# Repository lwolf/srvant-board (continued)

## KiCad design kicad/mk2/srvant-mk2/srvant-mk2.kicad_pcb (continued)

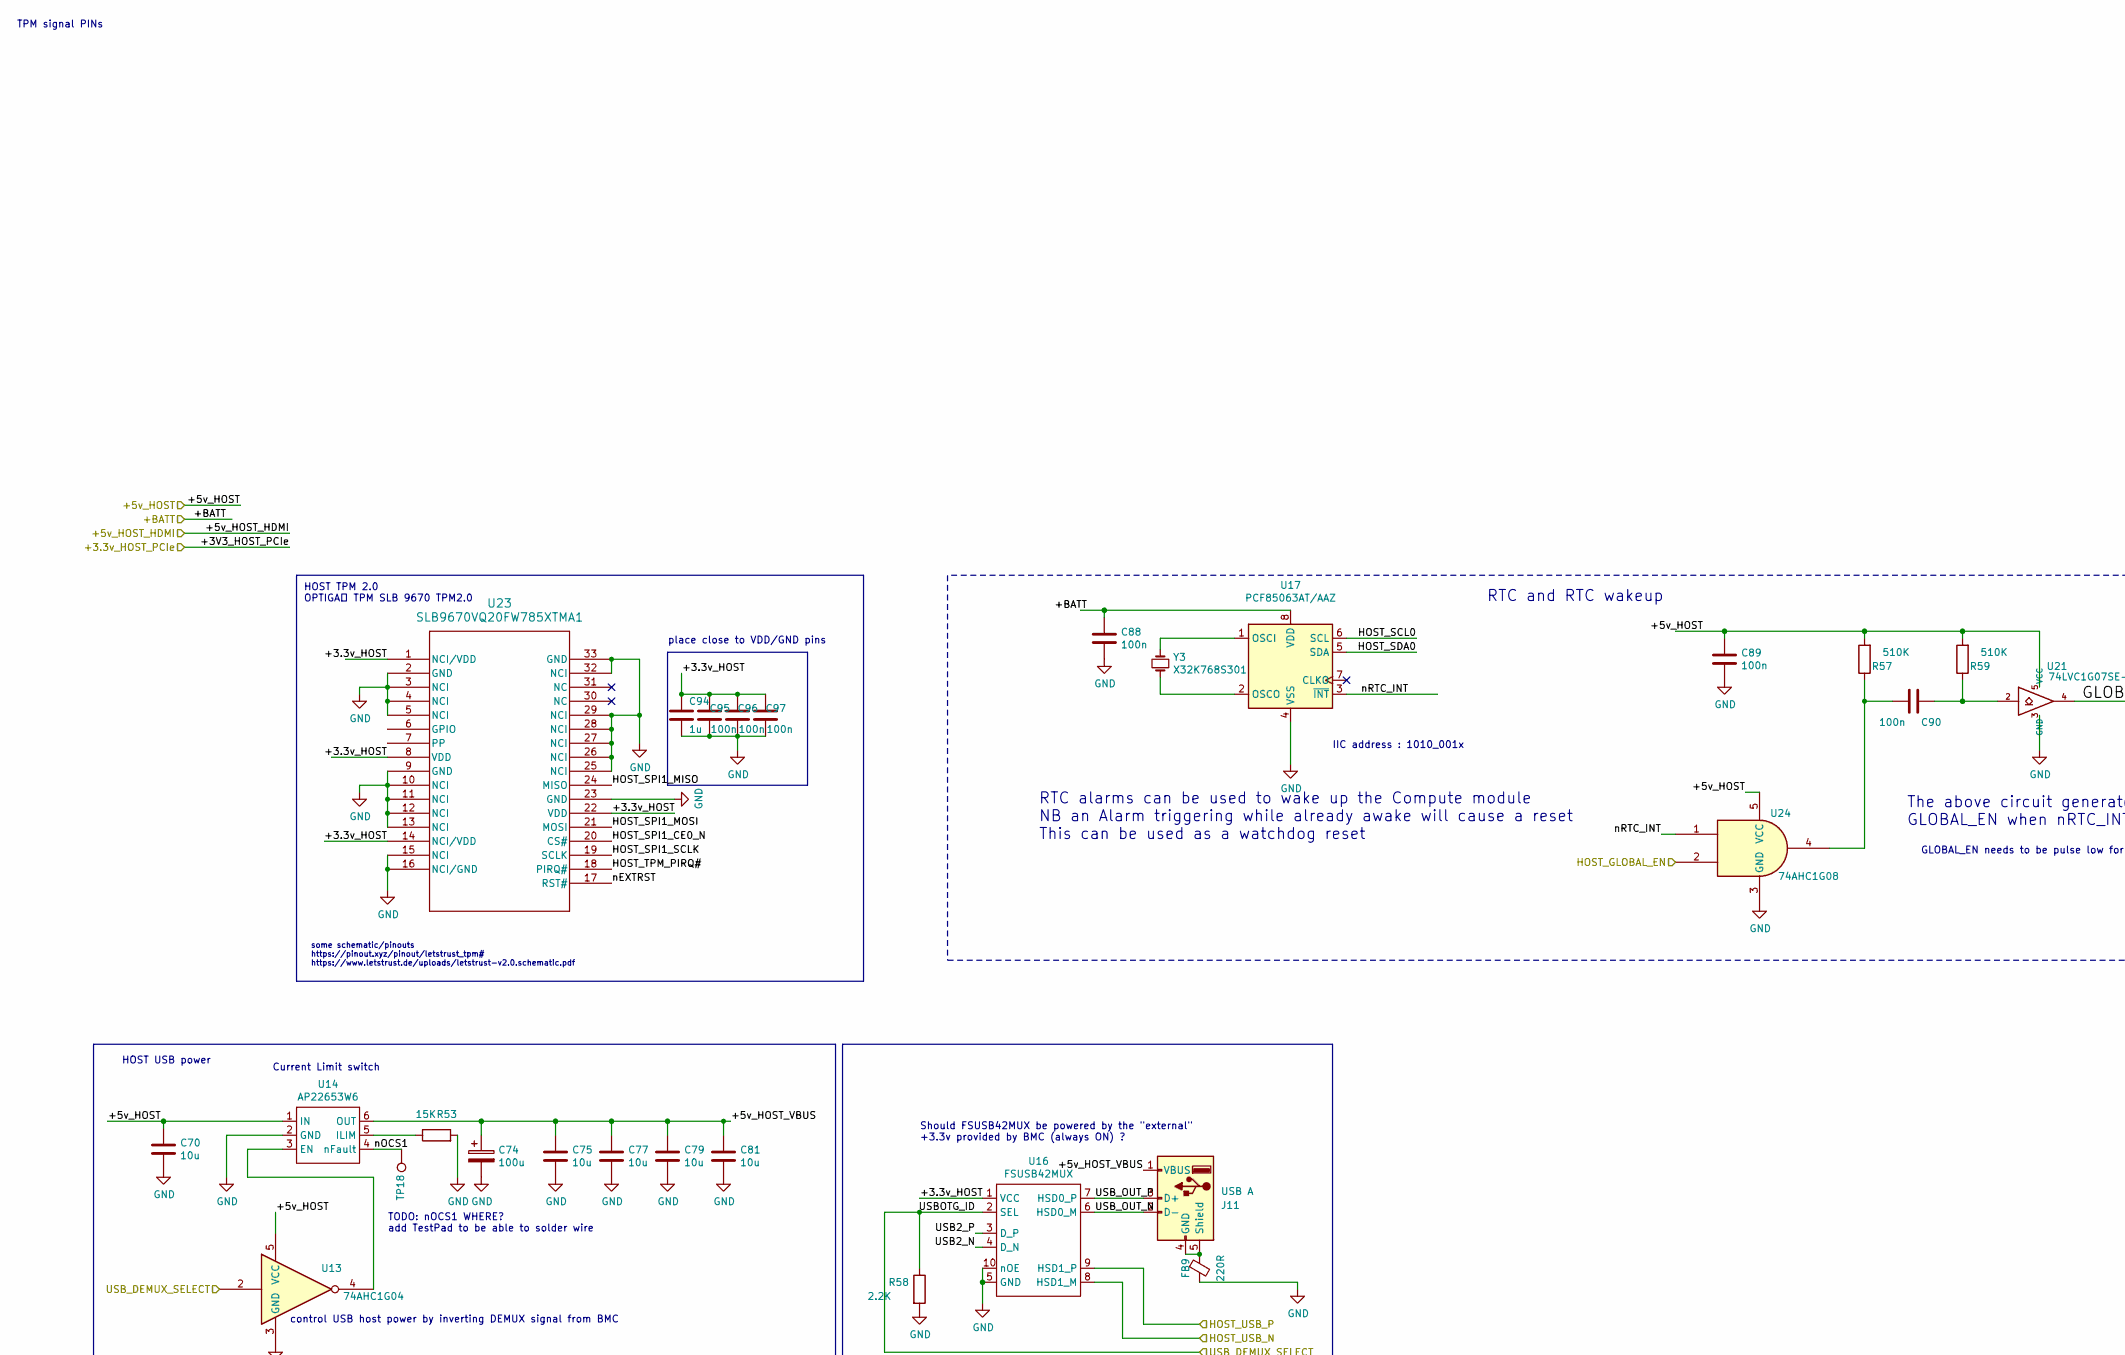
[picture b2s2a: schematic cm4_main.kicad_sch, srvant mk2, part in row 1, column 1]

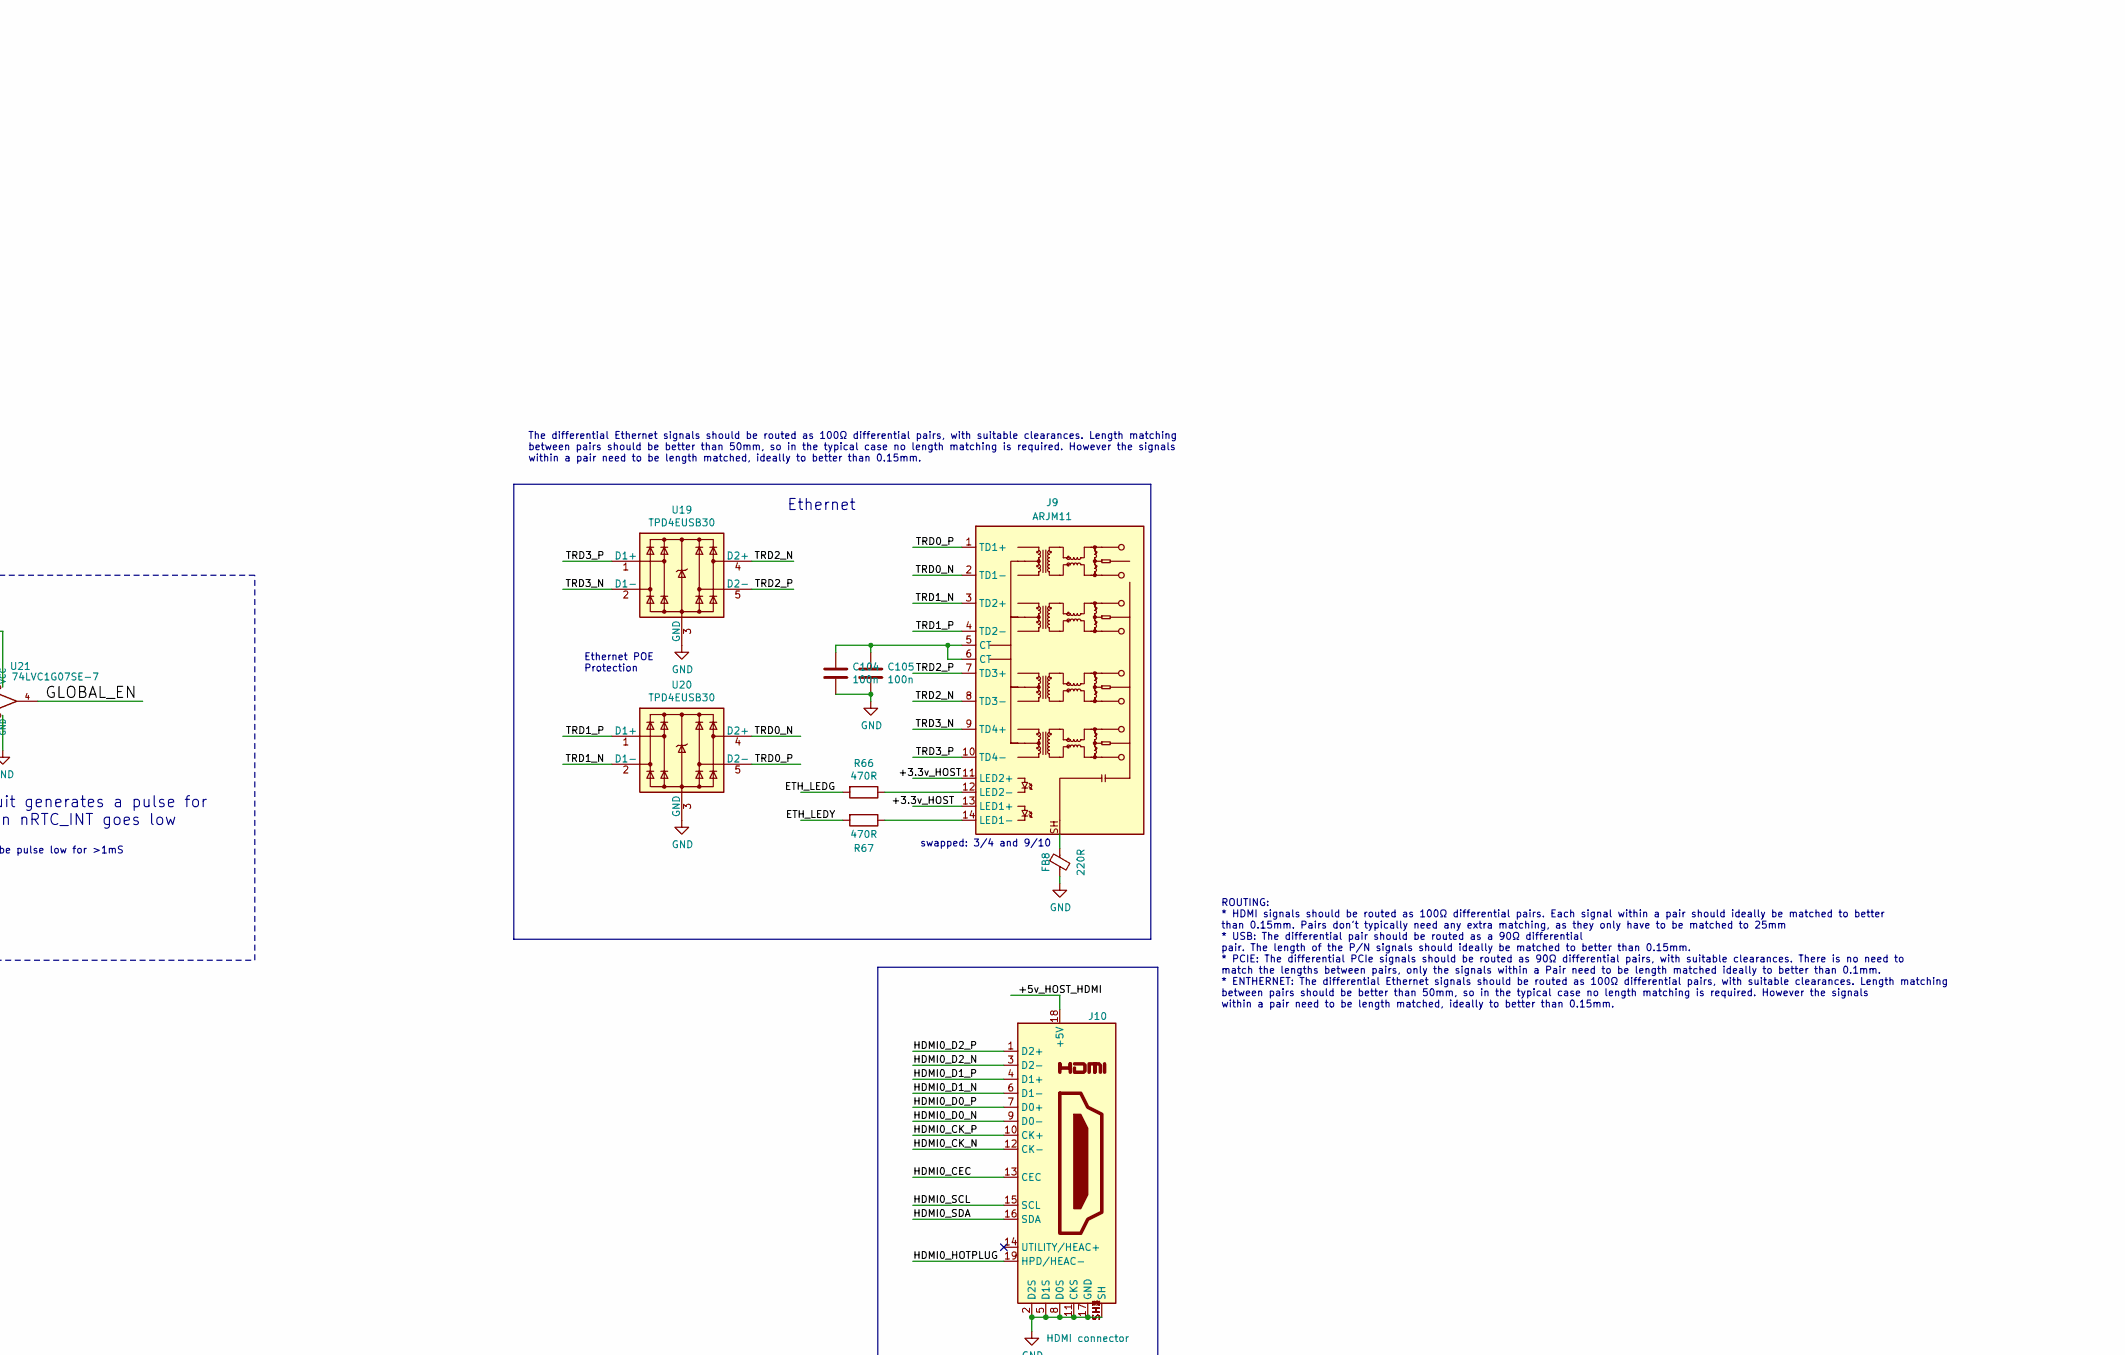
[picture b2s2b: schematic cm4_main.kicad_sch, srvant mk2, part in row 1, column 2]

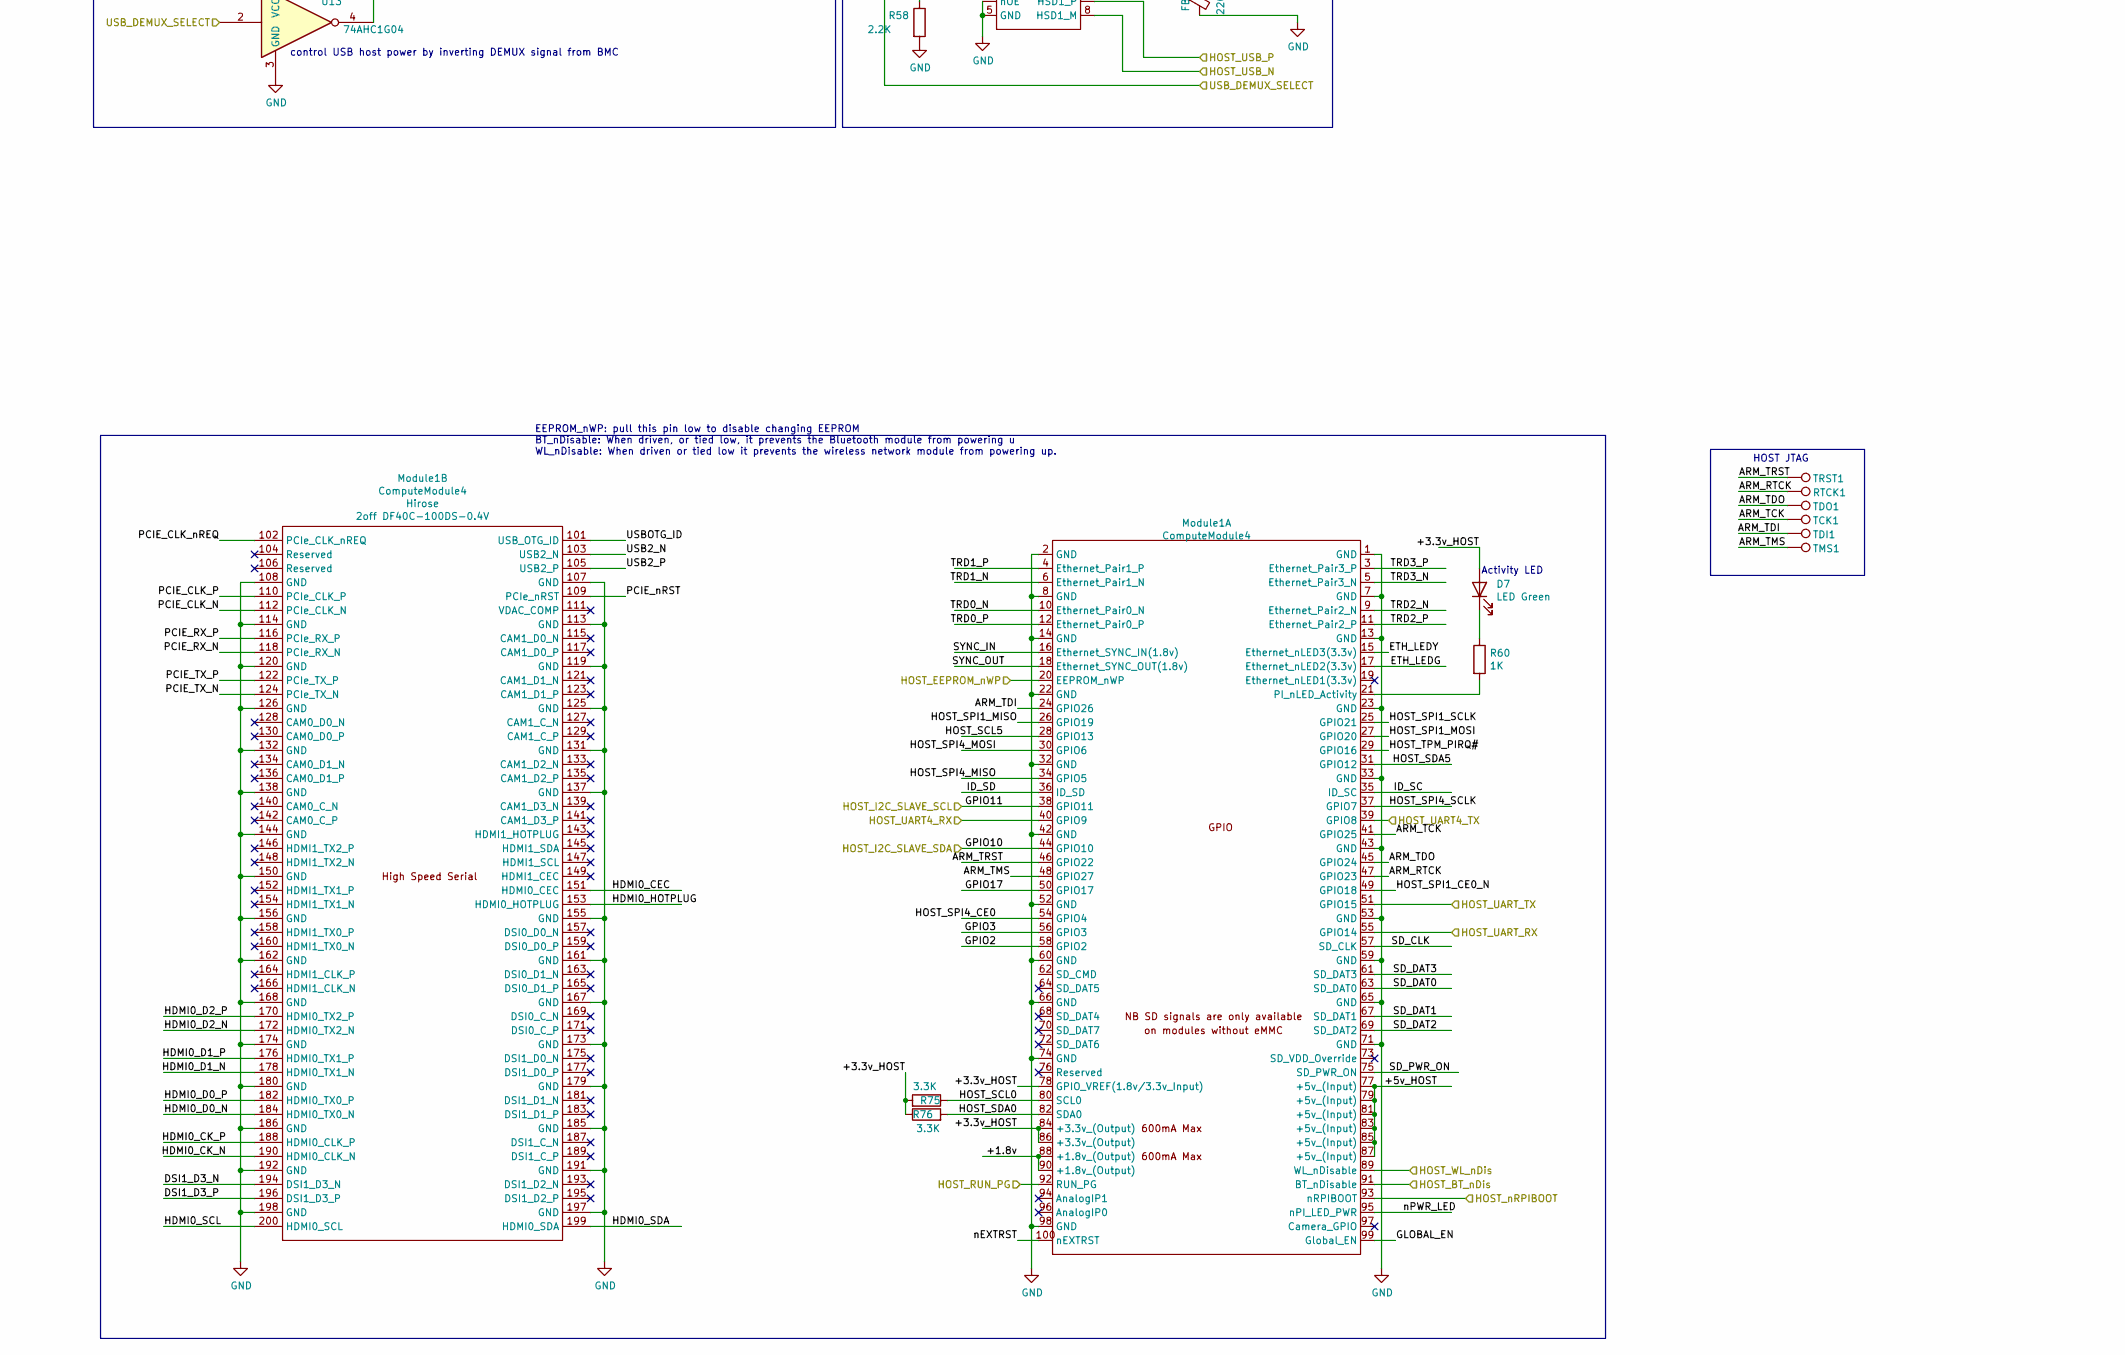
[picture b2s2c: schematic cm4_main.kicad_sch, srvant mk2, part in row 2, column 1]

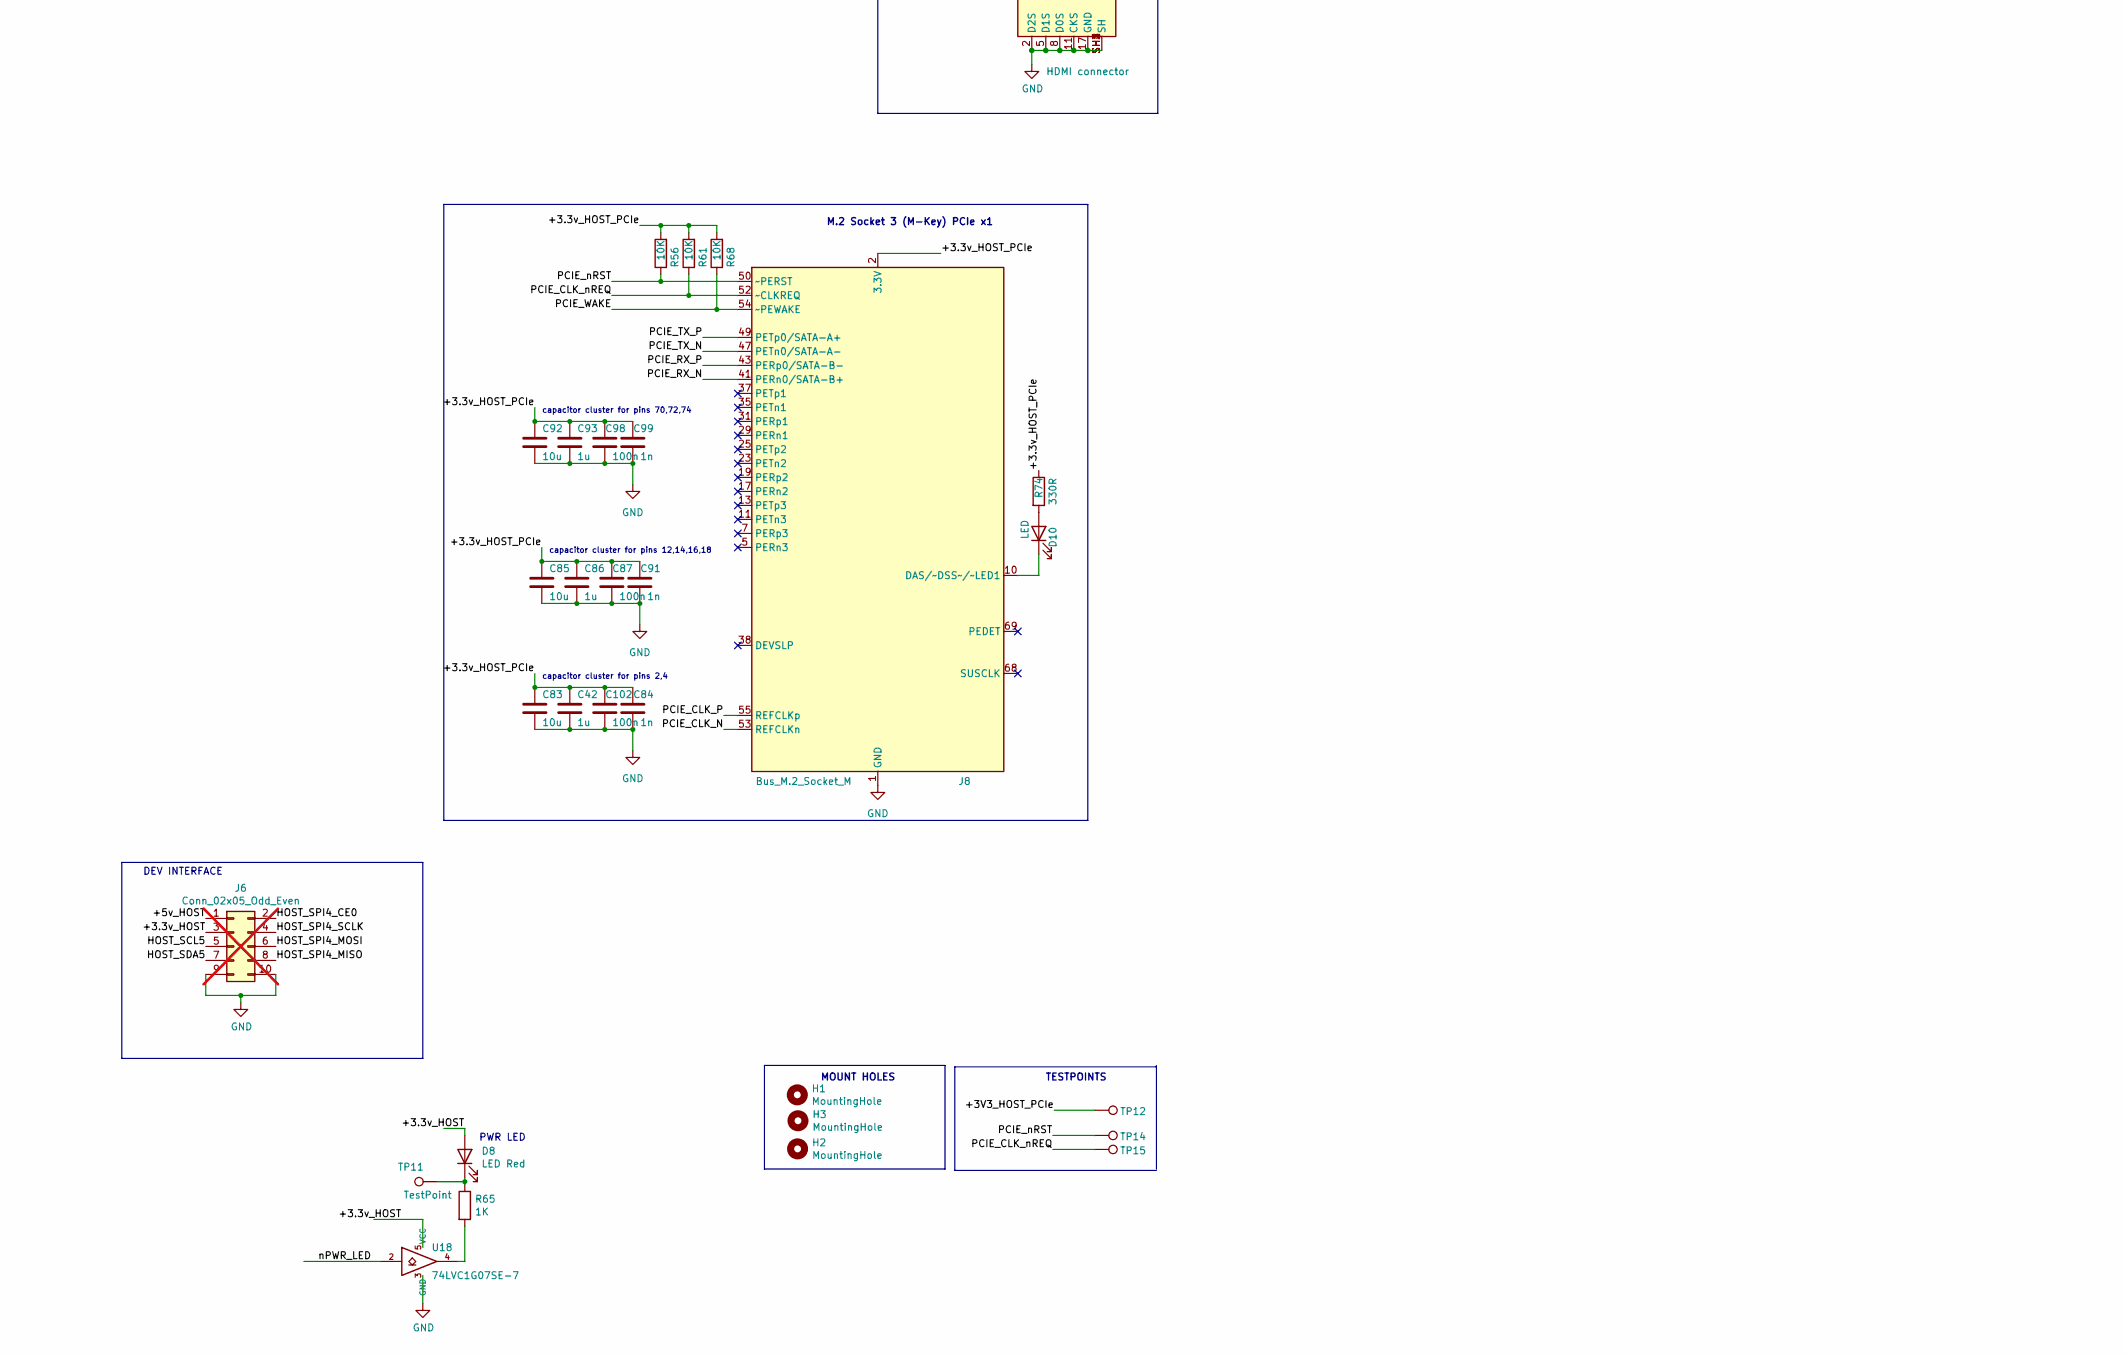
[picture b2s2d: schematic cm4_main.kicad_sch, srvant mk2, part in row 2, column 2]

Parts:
C42, C86, C93: 1u; C_0805_2012Metric; farnell# 3013481
C70, C75, C77, C79, C81, C83, C85, C92: 10u; C_0805_2012Metric; Part Description 10uF 10% 10V Ceramic Capacitor X7R 0805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; digikey# 490-14381-1-ND
C74: 100u; CP_EIA-7343-31_Kemet-D; Part Description Capacitor, SP-Cap, 100u, 6.3V, 15mR ESR; mouser# ECASD40J107M015K00
C84, C91, C99: 1n; C_0805_2012Metric; farnell# 2812395
C87, C98, C102: 100n; C_0805_2012Metric; Part Description 0.1uF 10% 16V Ceramic Capacitor X7R 040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; farnell# 3582682
C88, C89, C90, C95, C96, C97, C104, C105: 100n; C_0402_1005Metric; Part Description 0.1uF 10% 16V Ceramic Capacitor X7R 040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
C94: 1u; C_0402_1005Metric; mouser# 81-GRT155C81A105KE1D
D7: LED Green; LED_0603_1608Metric; Part Description Green 572nm LED Indication - Discrete 2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
D8: LED Red; LED_0603_1608Metric; Part Description Red 620nm LED Indication - Discrete 2.2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
D10: LED; LED_0603_1608Metric; Part Description Red 620nm LED Indication - Discrete 2.2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
FB8, FB9: 220R; R_0402_1005Metric; mouser# 81-BLM15PX221SH1D
H1, H2, H3: MountingHole; MountingHole_2.5mm_Pad_TopOnly; Part Description M2.5 mounting hole
J6: Conn_02x05_Odd_Even; PinHeader_2x05_P2.54mm_Vertical; Part Description PinHeader_2x05_P2.54mm_Vertical; not fitted
J8: Bus_M.2_Socket_M; 1-2199230-5
J9: ARJM11; RJ45_Wuerth_7499111446_Horizontal
J10: HDMI connector; HDMI-10029449-001RLF; Part Description HDMI Connector, Right Angle, 19 Contact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; farnell# 2614936
J11: USB A; CONN_GSB19110KEU_AMP; Part Description GSB19110KEU; farnell# 1860613
Module1: ComputeModule4; Raspberry-Pi-4-Compute-Module; Part Description 100 Position Connector Receptacle, Cent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
R53: 15K; R_0402_1005Metric; Part Description Resistor 15K M1005 1% 63mW
R56, R61, R68: 10K; R_0402_1005Metric
R57, R59: 510K; R_0402_1005Metric; Part Description Resistor 510K M1005 1% 63mW
R58: 2.2K; R_0402_1005Metric; Part Description Resistor 2.2K M1005 1% 63mW
R60, R65: 1K; R_0402_1005Metric; Part Description Resistor 1K M1005 1% 63mW
R66, R67: 470R; R_0402_1005Metric; Part Description Resistor 470R M1005 1% 63mW
R74: 330R; R_0402_1005Metric
R75, R76: 3.3K; R_0402_1005Metric
RTCK1: RTCK; TestPoint_Pad_D1.0mm
TCK1: TCK; TestPoint_Pad_D1.0mm
TDI1: TDI; TestPoint_Pad_D1.0mm
TDO1: TDO; TestPoint_Pad_D1.0mm
TMS1: TMS; TestPoint_Pad_D1.0mm
TP11: TestPoint; TestPoint_Pad_D1.0mm
TP12: 3v3_PCIe; TestPoint_Pad_D1.0mm
TP14: PCIe_nCLKREQ; TestPoint_Pad_D1.0mm
TP15: PCIe_nRST; TestPoint_Pad_D1.0mm
TP18: TestPoint_Pad_D1.0mm
TRST1: TRST; TestPoint_Pad_D1.0mm
U13: 74AHC1G04; SOT-23-5; mouser# 595-SN74AHC1G04DBVRG
U14: AP22653W6; SOT-23-6; Part Description Power Switch/Driver 1:1 P-Channel 2.1A 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; farnell# 3755402
U16: FSUSB42MUX; FSUSB42UMX; Part Description USB Switch IC 1 Channel 10-MSOP
U17: PCF85063AT/AAZ; SOIC-8_3.9x4.9mm_P1.27mm; Part Description Real Time Clock (RTC) IC Clock/Calendar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
U18, U21: 74LVC1G07SE-7; SOT-353_SC-70-5; Part Description Buffer, Non-Inverting 1 Element 1 Bit p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
U19, U20: TPD4EUSB30; USON-10_2.5x1.0mm_P0.5mm; Part Description Quad TVS diode for high speed signals (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
U23: SLB9670VQ20FW785XTMA1; QFN32_SLB9670VQ20FW785XTMA1_INF; mouser# 726-SLB9670V20FW785X
U24: 74AHC1G08; SOT-23-5; mouser# 595-SN74AHC1G08DBVR
Y3: X32K768S301; Crystal_SMD_2012-2Pin_2.0x1.2mm; Part Description Crystal 32.768KHz 7pF 20pmm; digikey# 535-14101-2-ND

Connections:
/bmc/BMC_HOST_BT_nDis: Module1.89 (WL_nDisable); also elsewhere on the board
/bmc/BMC_HOST_EEPROM_nWP: Module1.20 (EEPROM_nWP); also elsewhere on the board
/bmc/BMC_HOST_POST_COMPLETE: Module1.92 (RUN_PG); also elsewhere on the board
/bmc/BMC_HOST_POWER_OUT: U24.2; also elsewhere on the board
/bmc/BMC_HOST_WL_nDis: Module1.91 (BT_nDisable); also elsewhere on the board
/bmc/BMC_HOST_nRPIBOOT: Module1.93 (nRPIBOOT); also elsewhere on the board
/bmc/BMC_UART0_RX: Module1.55 (GPIO14); also elsewhere on the board
/bmc/BMC_UART0_TX: Module1.51 (GPIO15); also elsewhere on the board
/bmc/BMC_UART1_RX: Module1.39 (GPIO8); also elsewhere on the board
/bmc/BMC_UART1_TX: Module1.40 (GPIO9); also elsewhere on the board
/bmc/BMC_USB_HOST_N: U16.8 (HSD1_M); also elsewhere on the board
/bmc/BMC_USB_HOST_P: U16.9 (HSD1_P); also elsewhere on the board
/cm4/+1.8v: Module1.88 (+1.8v_(Output)), Module1.90 (+1.8v_(Output))
/cm4/+3.3v_HOST: C94.1, C95.2, C96.2, C97.2, D7.2 (A), D8.2 (A), J9.11 (LED2+), J9.13 (LED1+), Module1.78 (GPIO_VREF(1.8v/3.3v_Input)), Module1.84 (+3.3v_(Output)), Module1.86 (+3.3v_(Output)), R75.2, R76.1, U16.1 (VCC), U18.5 (VCC), U23.1 (NCI/VDD), U23.8 (VDD), U23.14 (NCI/VDD), U23.22 (VDD)
/cm4/+3.3v_HOST_PCIe: C42.1, C83.1, C84.1, C85.1, C86.1, C87.1, C91.1, C92.1, C93.1, C98.1, C99.1, C102.1, J8.2 (3.3V), J8.4 (3.3V), J8.12 (3.3V), J8.14 (3.3V), J8.16 (3.3V), J8.18 (3.3V), J8.70 (3.3V), J8.72 (3.3V), J8.74 (3.3V), R56.2, R61.2, R68.2, R74.1, TP12.1; also elsewhere on the board
/cm4/+5v_HOST: C70.1, C89.1, Module1.77 (+5v_(Input)), Module1.79 (+5v_(Input)), Module1.81 (+5v_(Input)), Module1.83 (+5v_(Input)), Module1.85 (+5v_(Input)), Module1.87 (+5v_(Input)), R57.2, R59.2, U13.5 (VCC), U14.1 (IN), U21.5 (VCC), U24.5 (VCC); also elsewhere on the board
/cm4/+5v_HOST_HDMI: J10.18 (+5V); also elsewhere on the board
/cm4/+5v_HOST_VBUS: C74.1, C75.1, C77.1, C79.1, C81.1, J11.1 (VBUS), U14.6 (OUT)
/cm4/+BATT: C88.1, U17.8 (VDD); also elsewhere on the board
/cm4/ARM_RTCK: Module1.47 (GPIO23), RTCK1.1
/cm4/ARM_TCK: Module1.41 (GPIO25), TCK1.1
/cm4/ARM_TDI: Module1.24 (GPIO26), TDI1.1
/cm4/ARM_TDO: Module1.45 (GPIO24), TDO1.1
/cm4/ARM_TMS: Module1.48 (GPIO27), TMS1.1
/cm4/ARM_TRST: Module1.46 (GPIO22), TRST1.1
/cm4/DSI1_D3_N: Module1.194 (DSI1_D3_N)
/cm4/DSI1_D3_P: Module1.196 (DSI1_D3_P)
/cm4/ETH_LEDG: Module1.17 (Ethernet_nLED2(3.3v)), R66.2
/cm4/ETH_LEDY: Module1.15 (Ethernet_nLED3(3.3v)), R67.2
/cm4/GLOBAL_EN: Module1.99 (Global_EN), U21.4
/cm4/GPIO2: Module1.58 (GPIO2)
/cm4/GPIO3: Module1.56 (GPIO3)
/cm4/GPIO10: Module1.44 (GPIO10); also elsewhere on the board
/cm4/GPIO11: Module1.38 (GPIO11); also elsewhere on the board
/cm4/GPIO17: Module1.50 (GPIO17)
/cm4/HDMI0_CEC: J10.13 (CEC), Module1.151 (HDMI0_CEC)
/cm4/HDMI0_CK_N: J10.12 (CK-), Module1.190 (HDMI0_CLK_N)
/cm4/HDMI0_CK_P: J10.10 (CK+), Module1.188 (HDMI0_CLK_P)
/cm4/HDMI0_D0_N: J10.9 (D0-), Module1.184 (HDMI0_TX0_N)
/cm4/HDMI0_D0_P: J10.7 (D0+), Module1.182 (HDMI0_TX0_P)
/cm4/HDMI0_D1_N: J10.6 (D1-), Module1.178 (HDMI0_TX1_N)
/cm4/HDMI0_D1_P: J10.4 (D1+), Module1.176 (HDMI0_TX1_P)
/cm4/HDMI0_D2_N: J10.3 (D2-), Module1.172 (HDMI0_TX2_N)
/cm4/HDMI0_D2_P: J10.1 (D2+), Module1.170 (HDMI0_TX2_P)
/cm4/HDMI0_HOTPLUG: J10.19 (HPD/HEAC-), Module1.153 (HDMI0_HOTPLUG)
/cm4/HDMI0_SCL: J10.15 (SCL), Module1.200 (HDMI0_SCL)
/cm4/HDMI0_SDA: J10.16 (SDA), Module1.199 (HDMI0_SDA)
/cm4/HOST_SCL0: Module1.80 (SCL0), R75.1, U17.6 (SCL)
/cm4/HOST_SCL5: J6.5, Module1.28 (GPIO13)
/cm4/HOST_SDA0: Module1.82 (SDA0), R76.2, U17.5 (SDA)
/cm4/HOST_SDA5: J6.7, Module1.31 (GPIO12)
/cm4/HOST_SPI1_CE0_N: Module1.49 (GPIO18), U23.20 (CS#)
/cm4/HOST_SPI1_MISO: Module1.26 (GPIO19), U23.24 (MISO)
/cm4/HOST_SPI1_MOSI: Module1.27 (GPIO20), U23.21 (MOSI)
/cm4/HOST_SPI1_SCLK: Module1.25 (GPIO21), U23.19 (SCLK)
/cm4/HOST_SPI4_CE0: J6.2, Module1.54 (GPIO4)
/cm4/HOST_SPI4_MISO: J6.8, Module1.34 (GPIO5)
/cm4/HOST_SPI4_MOSI: J6.6, Module1.30 (GPIO6)
/cm4/HOST_SPI4_SCLK: J6.4, Module1.37 (GPIO7)
/cm4/HOST_TPM_PIRQ#: Module1.29 (GPIO16), U23.18 (PIRQ#)
/cm4/ID_SC: Module1.35 (ID_SC)
/cm4/ID_SD: Module1.36 (ID_SD)
/cm4/PCIE_CLK_N: J8.53 (REFCLKn), Module1.112 (PCIe_CLK_N)
/cm4/PCIE_CLK_P: J8.55 (REFCLKp), Module1.110 (PCIe_CLK_P)
/cm4/PCIE_CLK_nREQ: J8.52 (~CLKREQ), Module1.102 (PCIe_CLK_nREQ), R61.1, TP15.1
/cm4/PCIE_RX_N: J8.41 (PERn0/SATA-B+), Module1.118 (PCIe_RX_N)
/cm4/PCIE_RX_P: J8.43 (PERp0/SATA-B-), Module1.116 (PCIe_RX_P)
/cm4/PCIE_TX_N: J8.47 (PETn0/SATA-A-), Module1.124 (PCIe_TX_N)
/cm4/PCIE_TX_P: J8.49 (PETp0/SATA-A+), Module1.122 (PCIe_TX_P)
/cm4/PCIE_WAKE: J8.54 (~PEWAKE), R68.1
/cm4/PCIE_nRST: J8.50 (~PERST), Module1.109 (PCIe_nRST), R56.1, TP14.1
/cm4/SD_CLK: Module1.57 (SD_CLK)
/cm4/SD_DAT0: Module1.63 (SD_DAT0)
/cm4/SD_DAT1: Module1.67 (SD_DAT1)
/cm4/SD_DAT2: Module1.69 (SD_DAT2)
/cm4/SD_DAT3: Module1.61 (SD_DAT3)
/cm4/SD_PWR_ON: Module1.75 (SD_PWR_ON)
/cm4/SYNC_IN: Module1.16 (Ethernet_SYNC_IN(1.8v))
/cm4/SYNC_OUT: Module1.18 (Ethernet_SYNC_OUT(1.8v))
/cm4/TRD0_N: J9.2 (TD1-), Module1.10 (Ethernet_Pair0_N), U20.4 (D2+), U20.7
/cm4/TRD0_P: J9.1 (TD1+), Module1.12 (Ethernet_Pair0_P), U20.5 (D2-), U20.6
/cm4/TRD1_N: J9.3 (TD2+), Module1.6 (Ethernet_Pair1_N), U20.2 (D1-), U20.9
/cm4/TRD1_P: J9.4 (TD2-), Module1.4 (Ethernet_Pair1_P), U20.1 (D1+), U20.10
/cm4/TRD2_N: J9.8 (TD3-), Module1.9 (Ethernet_Pair2_N), U19.4 (D2+), U19.7
/cm4/TRD2_P: J9.7 (TD3+), Module1.11 (Ethernet_Pair2_P), U19.5 (D2-), U19.6
/cm4/TRD3_N: J9.9 (TD4+), Module1.5 (Ethernet_Pair3_N), U19.2 (D1-), U19.9
/cm4/TRD3_P: J9.10 (TD4-), Module1.3 (Ethernet_Pair3_P), U19.1 (D1+), U19.10
/cm4/USB2_N: Module1.103 (USB2_N), U16.4 (D_N)
/cm4/USB2_P: Module1.105 (USB2_P), U16.3 (D_P)
/cm4/USBOTG_ID: Module1.101 (USB_OTG_ID), R58.1, U13.2, U16.2 (SEL); also elsewhere on the board
/cm4/USB_OUT_N: J11.2 (D-), U16.6 (HSD0_M)
/cm4/USB_OUT_P: J11.3 (D+), U16.7 (HSD0_P)
/cm4/nEXTRST: Module1.100 (nEXTRST), U23.17 (RST#)
/cm4/nOCS1: TP18.1, U14.4 (nFault)
/cm4/nPWR_LED: Module1.95 (nPI_LED_PWR), U18.2
/cm4/nRTC_INT: U17.3 (~INT), U24.1
unnamed: C90.1, R59.1, U21.2
unnamed: C90.2, R57.1, U24.4
unnamed: C104.1, C105.1, J9.5 (CT), J9.6 (CT)
unnamed: D7.1 (K), R60.1
unnamed: D8.1 (K), R65.1, TP11.1
unnamed: D10.2 (A), R74.2
unnamed: D10.1 (K), J8.10 (DAS/~DSS~/~LED1)
unnamed: FB8.1, J9.SH
unnamed: J9.14 (LED1-), R67.1
unnamed: J9.12 (LED2-), R66.1
unnamed: FB9.1, J11.4 (GND), J11.5 (Shield)
unnamed: Module1.21 (PI_nLED_Activity), R60.2
unnamed: R65.2, U18.4
unnamed: U13.4, U14.3 (EN)
unnamed: R53.1, U14.5 (ILIM)
unnamed: U17.1 (OSCI), Y3.2
unnamed: U17.2 (OSCO), Y3.1

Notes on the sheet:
Activity LED
place close to VDD/GND pins
The differential Ethernet signals should be routed as 100Ω differential pairs, with suitable clearances. Length matching between pairs should be better than 50mm, so in the typical case no length matching is required. However the signals within a pair need to be length matched, ideally to better th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
capacitor cluster for pins 12,14,16,18
HOST JTAG
IIC address : 1010_001x
Ethernet POE Protection
RTC and RTC wakeup
ROUTING: * HDMI signals should be routed as 100Ω differential pairs. Each signal within a pair should ideally be matched to better than 0.15mm. Pairs don't typically need any extra matching, as they only have to be matched to 25mm * USB: The differential pair should be routed as a 90Ω differential 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
HOST USB power
capacitor cluster for pins 70,72,74
swapped: 3/4 and 9/10
Ethernet
DEV INTERFACE
TESTPOINTS
TODO: nOCS1 WHERE? add TestPad to be able to solder wire
HOST TPM 2.0 OPTIGA™ TPM SLB 9670 TPM2.0
TPM signal PINs
EEPROM_nWP: pull this pin low to disable changing EEPROM BT_nDisable: When driven, or tied low, it prevents the Bluetooth module from powering u WL_nDisable: When driven or tied low it prevents the wireless network module from powering up.
some schematic/pinouts https://pinout.xyz/pinout/letstrust_tpm# https://www.letstrust.de/uploads/letstrust-v2.0.schematic.pdf
MOUNT HOLES
GLOBAL_EN needs to be pulse low for >1mS
capacitor cluster for pins 2,4
control USB host power by inverting DEMUX signal from BMC
Current Limit switch
M.2 Socket 3 (M-Key) PCIe x1
Should FSUSB42MUX be powered by the "external" +3.3v provided by BMC (always ON) ?
PWR LED
The above circuit generates a pulse for GLOBAL_EN when nRTC_INT goes low
RTC alarms can be used to wake up the Compute module NB an Alarm triggering while already awake will cause a reset This can be used as a watchdog reset
